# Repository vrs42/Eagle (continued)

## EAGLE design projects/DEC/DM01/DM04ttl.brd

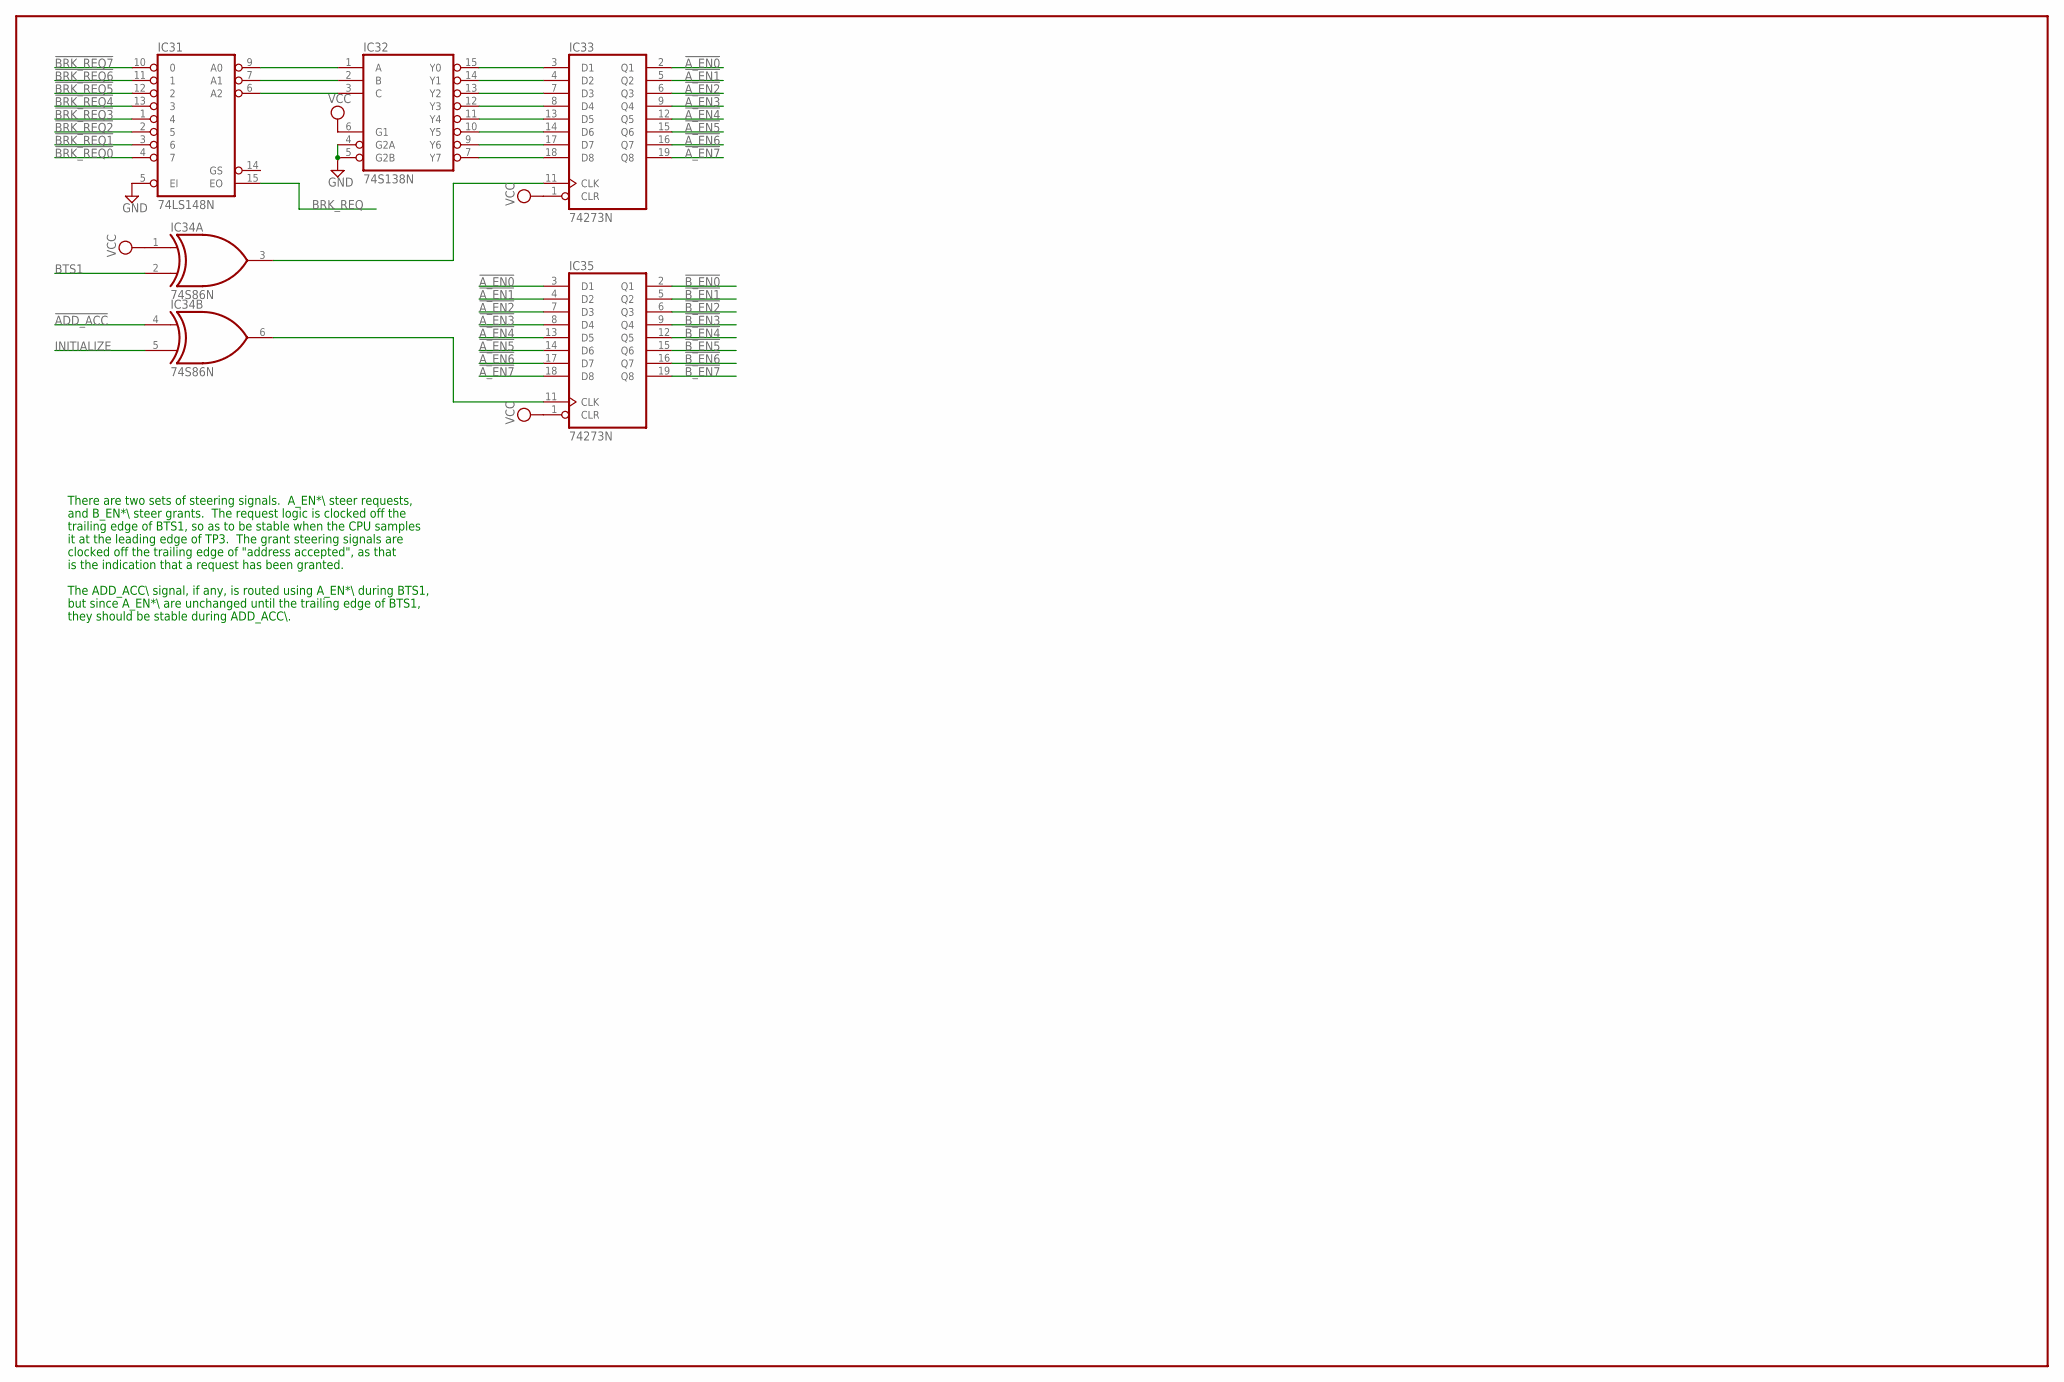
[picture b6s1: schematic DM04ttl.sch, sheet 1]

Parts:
IC31: 74LS148N; DIL16
IC32: 74S138N; DIL16
IC33, IC35: 74273N; DIL20
IC34: 74S86N; DIL14

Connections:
!ADD_ACC: IC34.4 (I0); also elsewhere on the board
!A_EN0: IC33.2 (Q1), IC35.3 (D1); also elsewhere on the board
!A_EN1: IC33.5 (Q2), IC35.4 (D2); also elsewhere on the board
!A_EN2: IC33.6 (Q3), IC35.7 (D3); also elsewhere on the board
!A_EN3: IC33.9 (Q4), IC35.8 (D4); also elsewhere on the board
!A_EN4: IC33.12 (Q5), IC35.13 (D5); also elsewhere on the board
!A_EN5: IC33.15 (Q6), IC35.14 (D6); also elsewhere on the board
!A_EN6: IC33.16 (Q7), IC35.17 (D7); also elsewhere on the board
!A_EN7: IC33.19 (Q8), IC35.18 (D8); also elsewhere on the board
!BRK_REQ0: IC31.4 (7); also elsewhere on the board
!BRK_REQ1: IC31.3 (6); also elsewhere on the board
!BRK_REQ2: IC31.2 (5); also elsewhere on the board
!BRK_REQ3: IC31.1 (4); also elsewhere on the board
!BRK_REQ4: IC31.13 (3); also elsewhere on the board
!BRK_REQ5: IC31.12 (2); also elsewhere on the board
!BRK_REQ6: IC31.11 (1); also elsewhere on the board
!BRK_REQ7: IC31.10 (0); also elsewhere on the board
!B_EN0: IC35.2 (Q1); also elsewhere on the board
!B_EN1: IC35.5 (Q2); also elsewhere on the board
!B_EN2: IC35.6 (Q3); also elsewhere on the board
!B_EN3: IC35.9 (Q4); also elsewhere on the board
!B_EN4: IC35.12 (Q5); also elsewhere on the board
!B_EN5: IC35.15 (Q6); also elsewhere on the board
!B_EN6: IC35.16 (Q7); also elsewhere on the board
!B_EN7: IC35.19 (Q8); also elsewhere on the board
BRK_REQ: IC31.15 (EO); also elsewhere on the board
BTS1: IC34.2 (I1); also elsewhere on the board
GND: IC31.5 (EI), IC31.8 (GND), IC32.4 (G2A), IC32.5 (G2B), IC32.8 (GND), IC33.10 (GND), IC34.7 (GND), IC35.10 (GND); also elsewhere on the board
INITIALIZE: IC34.5 (I1); also elsewhere on the board
unnamed: IC31.6 (A2), IC32.3 (C)
unnamed: IC34.6 (O), IC35.11 (CLK)
unnamed: IC31.7 (A1), IC32.2 (B)
unnamed: IC31.9 (A0), IC32.1 (A)
unnamed: IC32.15 (Y0), IC33.3 (D1)
unnamed: IC32.7 (Y7), IC33.18 (D8)
unnamed: IC32.9 (Y6), IC33.17 (D7)
unnamed: IC32.10 (Y5), IC33.14 (D6)
unnamed: IC32.11 (Y4), IC33.13 (D5)
unnamed: IC32.12 (Y3), IC33.8 (D4)
unnamed: IC32.13 (Y2), IC33.7 (D3)
unnamed: IC32.14 (Y1), IC33.4 (D2)
unnamed: IC33.11 (CLK), IC34.3 (O)
VCC: IC31.16 (VCC), IC32.6 (G1), IC32.16 (VCC), IC33.1 (CLR), IC33.20 (VCC), IC34.1 (I0), IC34.14 (VCC), IC35.1 (CLR), IC35.20 (VCC); also elsewhere on the board

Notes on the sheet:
There are two sets of steering signals. A_EN*\\ steer requests,
and B_EN*\\ steer grants. The request logic is clocked off the
trailing edge of BTS1, so as to be stable when the CPU samples
it at the leading edge of TP3. The grant steering signals are
clocked off the trailing edge of "address accepted", as that
is the indication that a request has been granted.
The ADD_ACC\\ signal, if any, is routed using A_EN*\\ during BTS1,
but since A_EN*\\ are unchanged until the trailing edge of BTS1,
they should be stable during ADD_ACC\\.

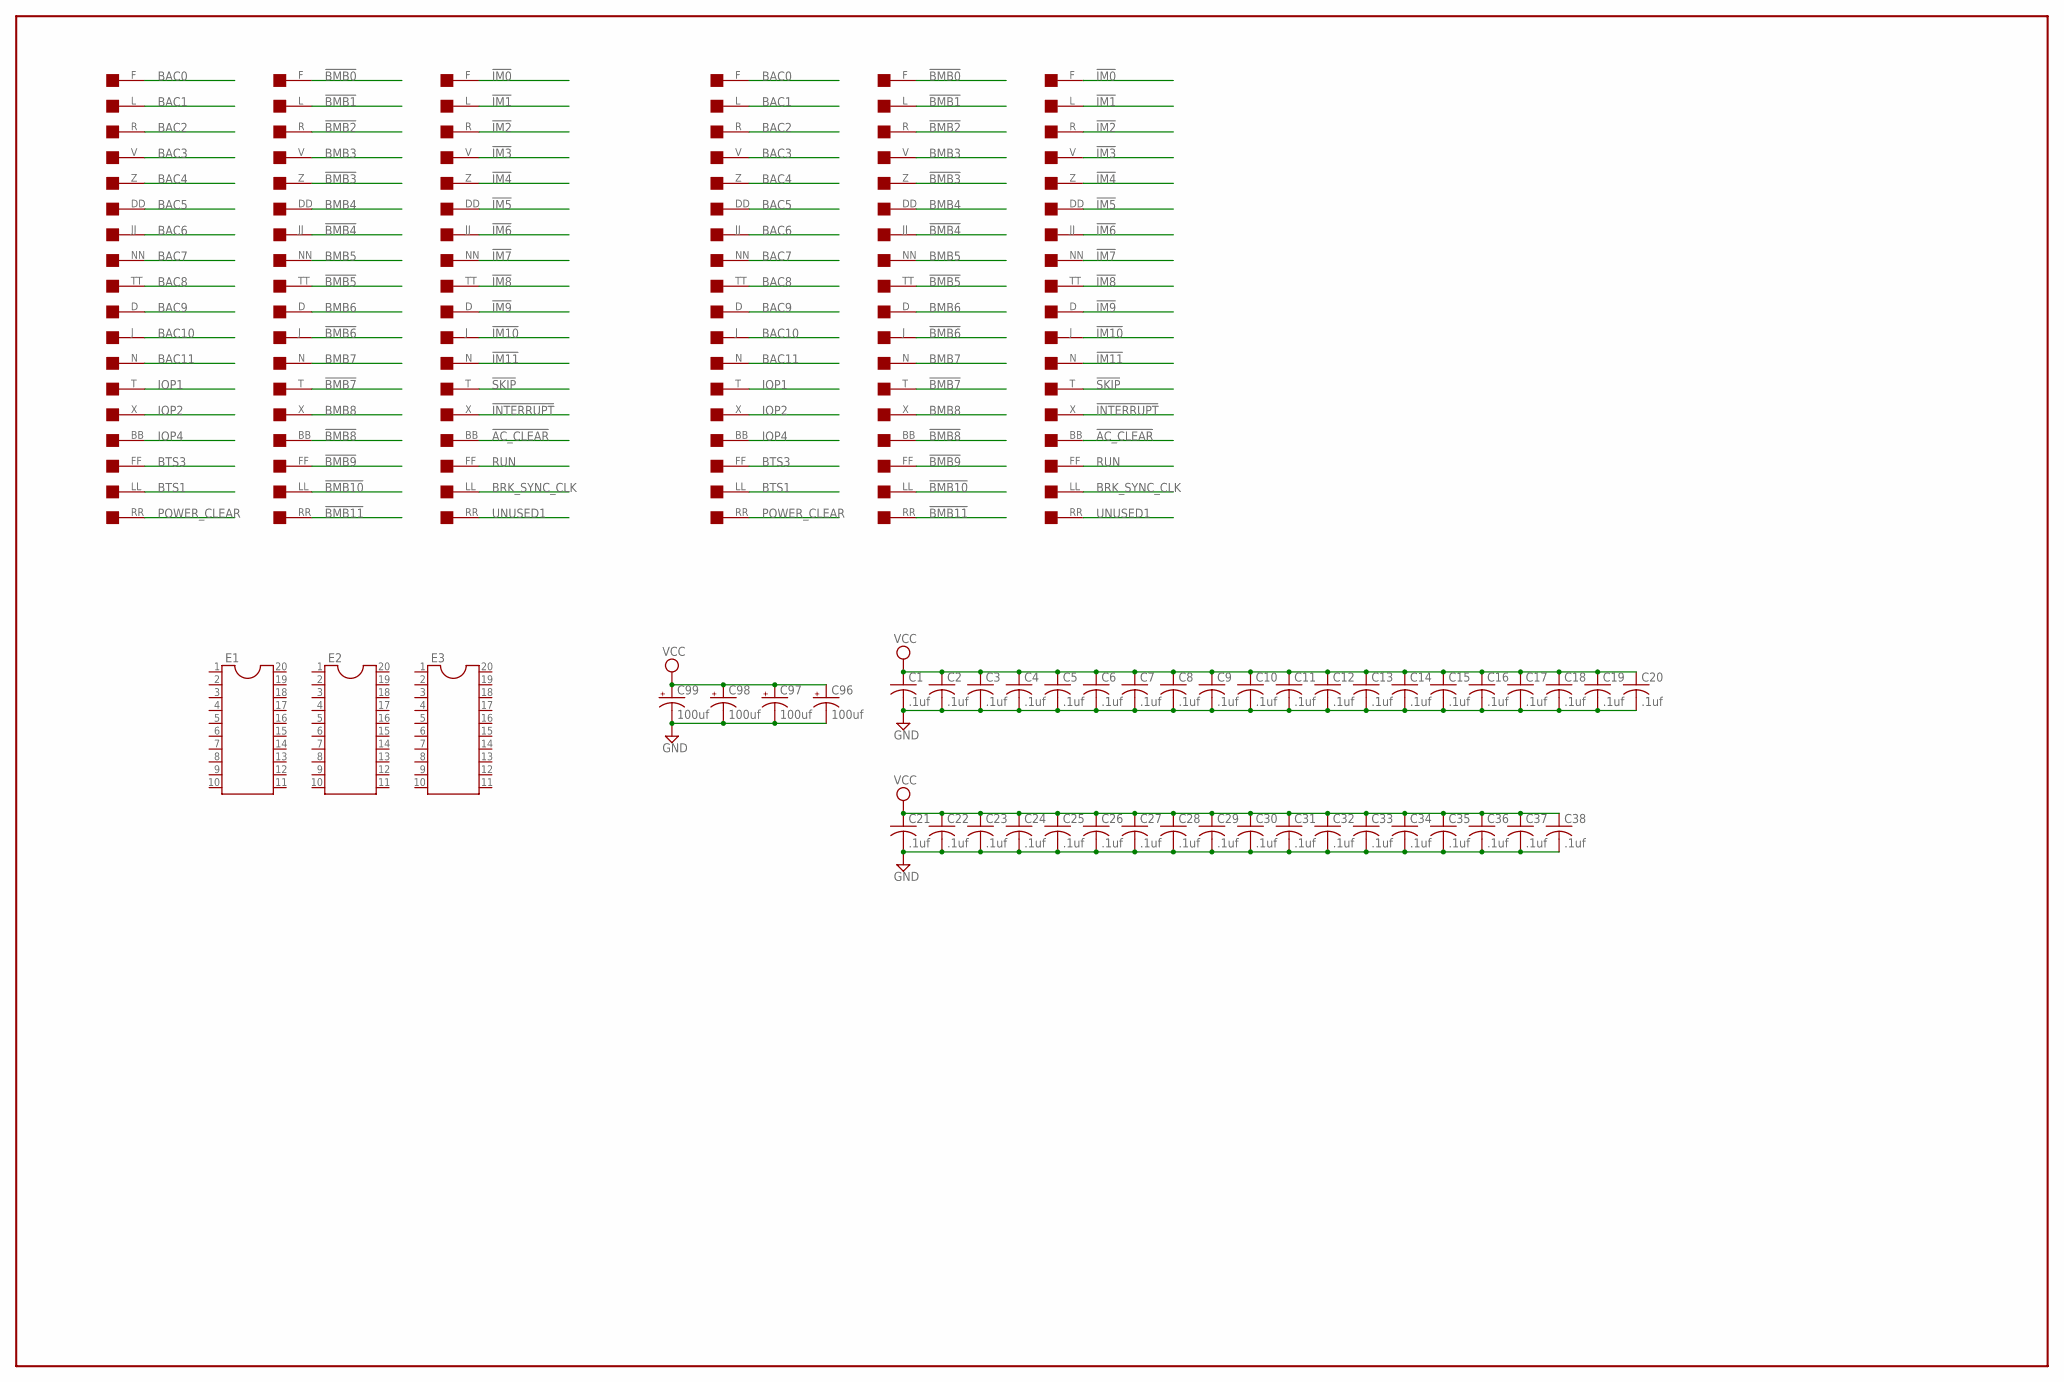
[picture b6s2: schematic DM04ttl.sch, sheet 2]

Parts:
AC0, AC1: BC08J; DEC40PINV
BAC0, BAC1: BC08J; DEC40PINV
BMB0, BMB1: BC08J; DEC40PINV
C1, C2, C3, C4, C5, C6, C7, C8, C9, C10, C11, C12, C13, C14, C15, C16, C17, C18, C19, C20, C21, C22, C23, C24, C25, C26, C27, C28, C29, C30, C31, C32, C33, C34, C35, C36, C37, C38: .1uf; C050-025X075
C96, C97, C98, C99: 100uf; E22-6
E1, E2, E3: DIL20

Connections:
!AC_CLEAR: AC0.BB (1), AC1.BB (1)
!BMB0: BMB0.F (1), BMB1.F (1)
!BMB1: BMB0.L (1), BMB1.L (1)
!BMB2: BMB0.R (1), BMB1.R (1)
!BMB3: BMB0.Z (1), BMB1.Z (1)
!BMB4: BMB0.JJ (1), BMB1.JJ (1)
!BMB5: BMB0.TT (1), BMB1.TT (1)
!BMB6: BMB0.J (1), BMB1.J (1)
!BMB7: BMB0.T (1), BMB1.T (1)
!BMB8: BMB0.BB (1), BMB1.BB (1)
!BMB9: BMB0.FF (1), BMB1.FF (1)
!BMB10: BMB0.LL (1), BMB1.LL (1)
!BMB11: BMB0.RR (1), BMB1.RR (1)
!IM0: AC0.F (1), AC1.F (1)
!IM1: AC0.L (1), AC1.L (1)
!IM2: AC0.R (1), AC1.R (1)
!IM3: AC0.V (1), AC1.V (1)
!IM4: AC0.Z (1), AC1.Z (1)
!IM5: AC0.DD (1), AC1.DD (1)
!IM6: AC0.JJ (1), AC1.JJ (1)
!IM7: AC0.NN (1), AC1.NN (1)
!IM8: AC0.TT (1), AC1.TT (1)
!IM9: AC0.D (1), AC1.D (1)
!IM10: AC0.J (1), AC1.J (1)
!IM11: AC0.N (1), AC1.N (1)
!INTERRUPT: AC0.X (1), AC1.X (1)
!SKIP: AC0.T (1), AC1.T (1)
BAC0: BAC0.F (1), BAC1.F (1)
BAC1: BAC0.L (1), BAC1.L (1)
BAC2: BAC0.R (1), BAC1.R (1)
BAC3: BAC0.V (1), BAC1.V (1)
BAC4: BAC0.Z (1), BAC1.Z (1)
BAC5: BAC0.DD (1), BAC1.DD (1)
BAC6: BAC0.JJ (1), BAC1.JJ (1)
BAC7: BAC0.NN (1), BAC1.NN (1)
BAC8: BAC0.TT (1), BAC1.TT (1)
BAC9: BAC0.D (1), BAC1.D (1)
BAC10: BAC0.J (1), BAC1.J (1)
BAC11: BAC0.N (1), BAC1.N (1)
BMB3: BMB0.V (1), BMB1.V (1)
BMB4: BMB0.DD (1), BMB1.DD (1)
BMB5: BMB0.NN (1), BMB1.NN (1)
BMB6: BMB0.D (1), BMB1.D (1)
BMB7: BMB0.N (1), BMB1.N (1)
BMB8: BMB0.X (1), BMB1.X (1)
BRK_SYNC_CLK: AC0.LL (1), AC1.LL (1)
BTS1: BAC0.LL (1), BAC1.LL (1); also elsewhere on the board
BTS3: BAC0.FF (1), BAC1.FF (1)
GND: AC0.A (GND), AC0.AA (GND), AC0.B (GND), AC0.C (GND), AC0.CC (GND), AC0.E (GND), AC0.EE (GND), AC0.H (GND), AC0.HH (GND), AC0.K (GND), AC0.KK (GND), AC0.M (GND), AC0.MM (GND), AC0.P (GND), AC0.PP (GND), AC0.S (GND), AC0.SS (GND), AC0.U (GND), AC0.UU (GND), AC0.VV (GND), AC0.W (GND), AC0.Y (GND), AC1.A (GND), AC1.AA (GND), AC1.B (GND), AC1.C (GND), AC1.CC (GND), AC1.E (GND), AC1.EE (GND), AC1.H (GND), AC1.HH (GND), AC1.K (GND), AC1.KK (GND), AC1.M (GND), AC1.MM (GND), AC1.P (GND), AC1.PP (GND), AC1.S (GND), AC1.SS (GND), AC1.U (GND), AC1.UU (GND), AC1.VV (GND), AC1.W (GND), AC1.Y (GND), BAC0.A (GND), BAC0.AA (GND), BAC0.B (GND), BAC0.C (GND), BAC0.CC (GND), BAC0.E (GND), BAC0.EE (GND), BAC0.H (GND), BAC0.HH (GND), BAC0.K (GND), BAC0.KK (GND), BAC0.M (GND), BAC0.MM (GND), BAC0.P (GND), BAC0.PP (GND), BAC0.S (GND), BAC0.SS (GND), BAC0.U (GND), BAC0.UU (GND), BAC0.VV (GND), BAC0.W (GND), BAC0.Y (GND), BAC1.A (GND), BAC1.AA (GND), BAC1.B (GND), BAC1.C (GND), BAC1.CC (GND), BAC1.E (GND), BAC1.EE (GND), BAC1.H (GND), BAC1.HH (GND), BAC1.K (GND), BAC1.KK (GND), BAC1.M (GND), BAC1.MM (GND), BAC1.P (GND), BAC1.PP (GND), BAC1.S (GND), BAC1.SS (GND), BAC1.U (GND), BAC1.UU (GND), BAC1.VV (GND), BAC1.W (GND), BAC1.Y (GND), BMB0.A (GND), BMB0.AA (GND), BMB0.B (GND), BMB0.C (GND), BMB0.CC (GND), BMB0.E (GND), BMB0.EE (GND), BMB0.H (GND), BMB0.HH (GND), BMB0.K (GND), BMB0.KK (GND), BMB0.M (GND), BMB0.MM (GND), BMB0.P (GND), BMB0.PP (GND), BMB0.S (GND), BMB0.SS (GND), BMB0.U (GND), BMB0.UU (GND), BMB0.VV (GND), BMB0.W (GND), BMB0.Y (GND), BMB1.A (GND), BMB1.AA (GND), BMB1.B (GND), BMB1.C (GND), BMB1.CC (GND), BMB1.E (GND), BMB1.EE (GND), BMB1.H (GND), BMB1.HH (GND), BMB1.K (GND), BMB1.KK (GND), BMB1.M (GND), BMB1.MM (GND), BMB1.P (GND), BMB1.PP (GND), BMB1.S (GND), BMB1.SS (GND), BMB1.U (GND), BMB1.UU (GND), BMB1.VV (GND), BMB1.W (GND), BMB1.Y (GND), C1.2, C2.2, C3.2, C4.2, C5.2, C6.2, C7.2, C8.2, C9.2, C10.2, C11.2, C12.2, C13.2, C14.2, C15.2, C16.2, C17.2, C18.2, C19.2, C20.2, C21.2, C22.2, C23.2, C24.2, C25.2, C26.2, C27.2, C28.2, C29.2, C30.2, C31.2, C32.2, C33.2, C34.2, C35.2, C36.2, C37.2, C38.2, C96.-, C97.-, C98.-, C99.-; also elsewhere on the board
IOP1: BAC0.T (1), BAC1.T (1)
IOP2: BAC0.X (1), BAC1.X (1)
IOP4: BAC0.BB (1), BAC1.BB (1)
POWER_CLEAR: BAC0.RR (1), BAC1.RR (1)
RUN: AC0.FF (1), AC1.FF (1)
UNUSED1: AC0.RR (1), AC1.RR (1)
VCC: C1.1, C2.1, C3.1, C4.1, C5.1, C6.1, C7.1, C8.1, C9.1, C10.1, C11.1, C12.1, C13.1, C14.1, C15.1, C16.1, C17.1, C18.1, C19.1, C20.1, C21.1, C22.1, C23.1, C24.1, C25.1, C26.1, C27.1, C28.1, C29.1, C30.1, C31.1, C32.1, C33.1, C34.1, C35.1, C36.1, C37.1, C38.1, C96.+, C97.+, C98.+, C99.+; also elsewhere on the board

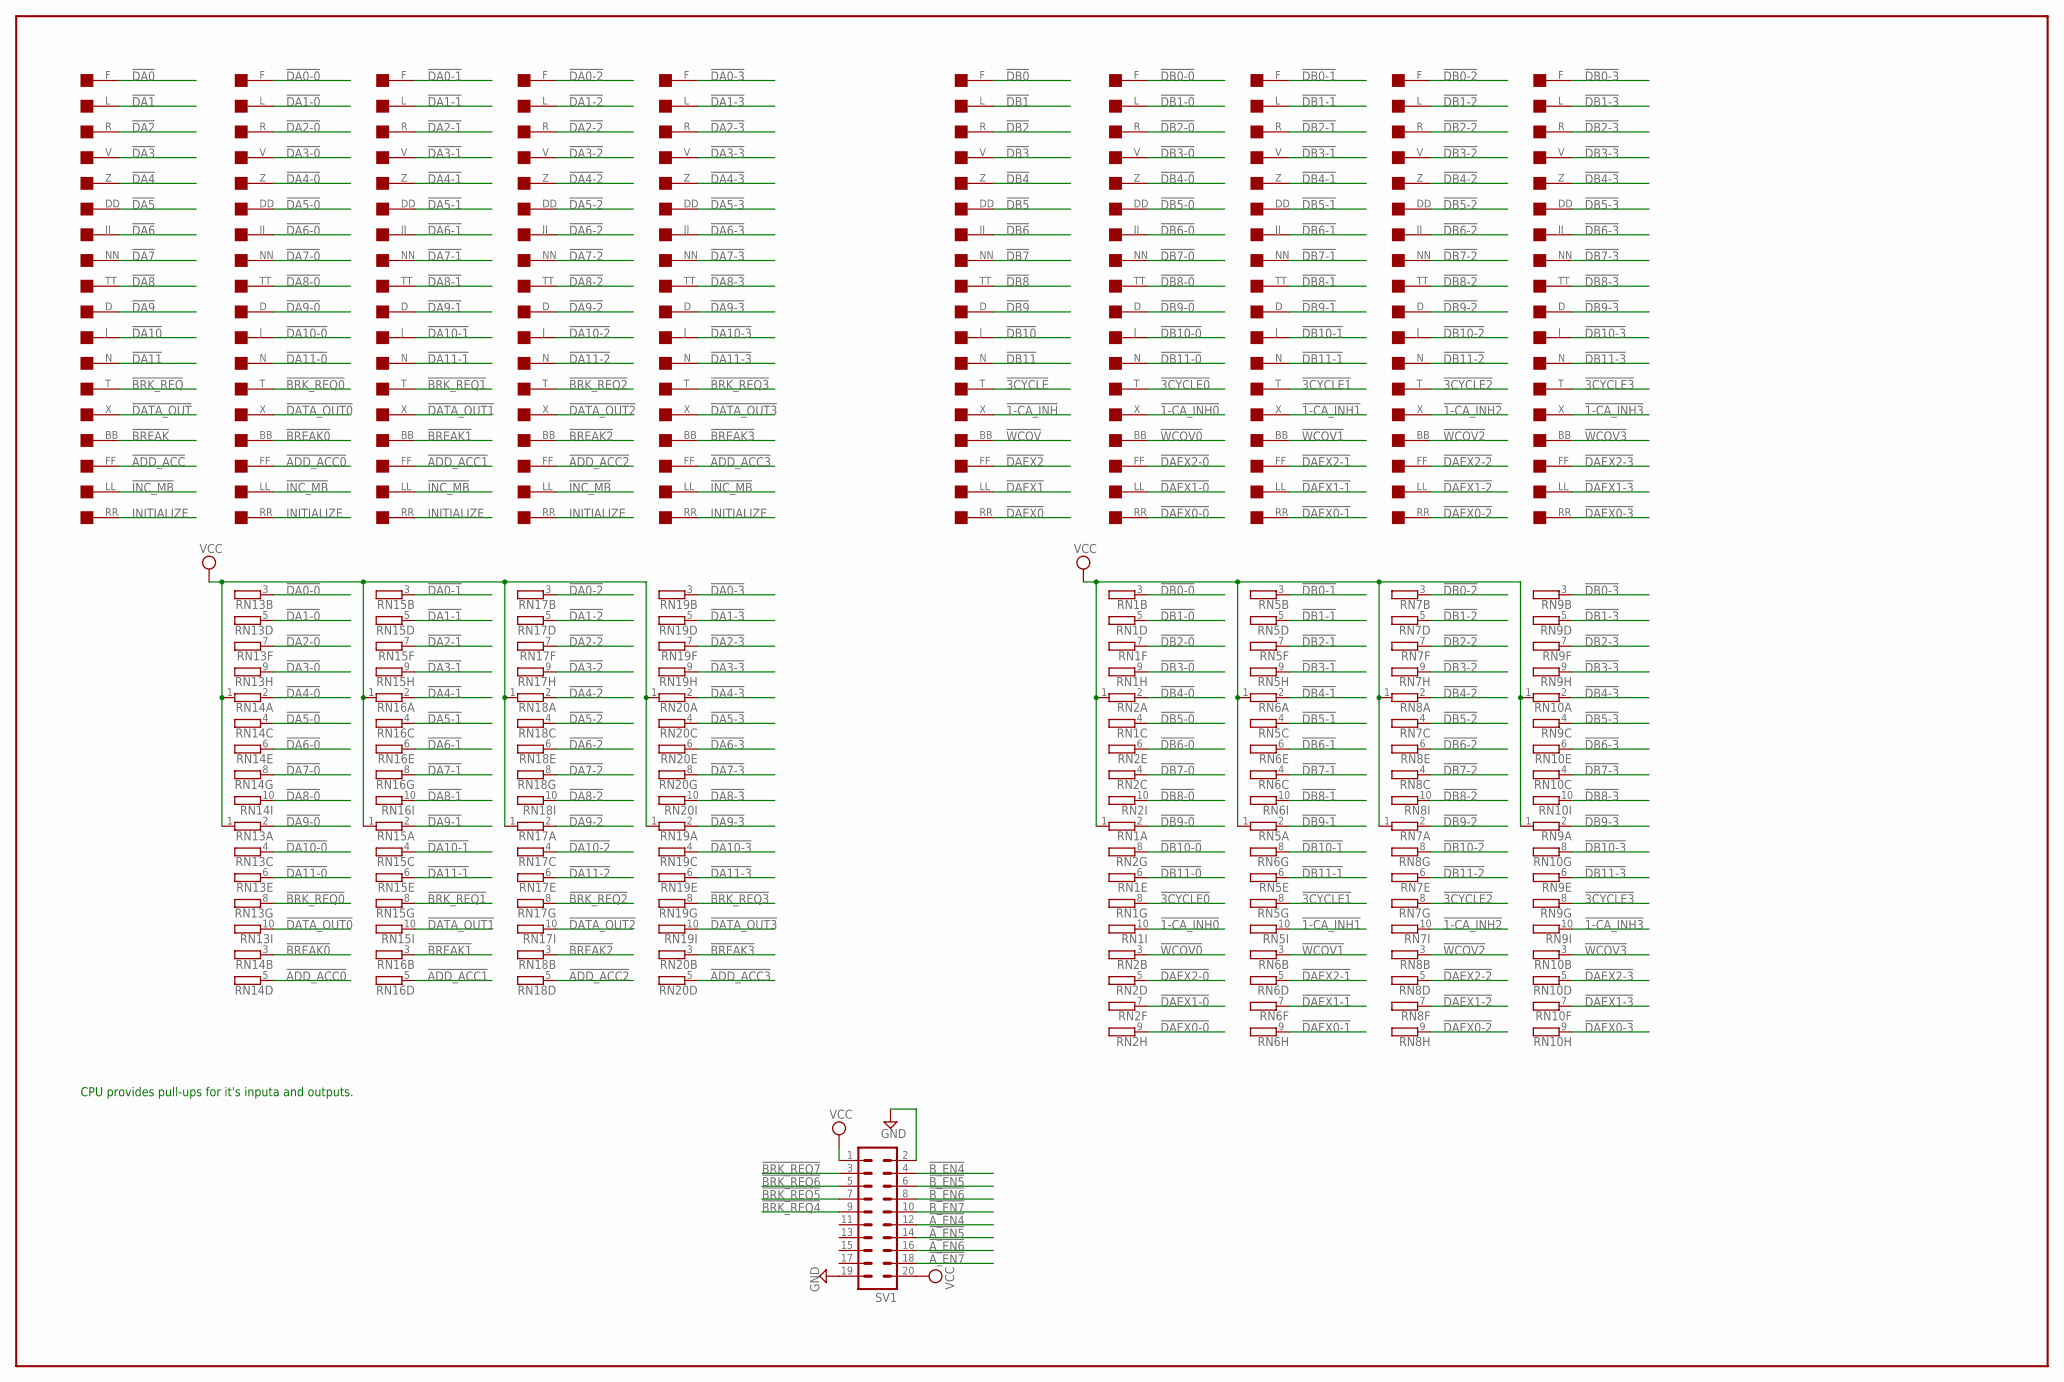
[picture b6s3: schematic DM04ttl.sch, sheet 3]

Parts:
ADDRESS, ADDRESS0, ADDRESS1, ADDRESS2, ADDRESS3: BC08J; DEC40PINV
DATA, DATA0, DATA1, DATA2, DATA3: BC08J; DEC40PINV
RN1, RN2, RN5, RN6, RN7, RN8, RN9, RN10, RN13, RN14, RN15, RN16, RN17, RN18, RN19, RN20: GE09R; SIL10
SV1: MA10-2

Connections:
!1-CA_INH: DATA.X (1); also elsewhere on the board
!1-CA_INH0: DATA0.X (1), RN1.10 (2); also elsewhere on the board
!1-CA_INH1: DATA1.X (1), RN5.10 (2); also elsewhere on the board
!1-CA_INH2: DATA2.X (1), RN7.10 (2); also elsewhere on the board
!1-CA_INH3: DATA3.X (1), RN9.10 (2); also elsewhere on the board
!3CYCLE: DATA.T (1); also elsewhere on the board
!3CYCLE0: DATA0.T (1), RN1.8 (2); also elsewhere on the board
!3CYCLE1: DATA1.T (1), RN5.8 (2); also elsewhere on the board
!3CYCLE2: DATA2.T (1), RN7.8 (2); also elsewhere on the board
!3CYCLE3: DATA3.T (1), RN9.8 (2); also elsewhere on the board
!ADD_ACC: ADDRESS.FF (1); also elsewhere on the board
!ADD_ACC0: ADDRESS0.FF (1), RN14.5 (2); also elsewhere on the board
!ADD_ACC1: ADDRESS1.FF (1), RN16.5 (2); also elsewhere on the board
!ADD_ACC2: ADDRESS2.FF (1), RN18.5 (2); also elsewhere on the board
!ADD_ACC3: ADDRESS3.FF (1), RN20.5 (2); also elsewhere on the board
!A_EN4: SV1.12; also elsewhere on the board
!A_EN5: SV1.14; also elsewhere on the board
!A_EN6: SV1.16; also elsewhere on the board
!A_EN7: SV1.18; also elsewhere on the board
!BREAK: ADDRESS.BB (1); also elsewhere on the board
!BREAK0: ADDRESS0.BB (1), RN14.3 (2); also elsewhere on the board
!BREAK1: ADDRESS1.BB (1), RN16.3 (2); also elsewhere on the board
!BREAK2: ADDRESS2.BB (1), RN18.3 (2); also elsewhere on the board
!BREAK3: ADDRESS3.BB (1), RN20.3 (2); also elsewhere on the board
!BRK_REQ: ADDRESS.T (1); also elsewhere on the board
!BRK_REQ0: ADDRESS0.T (1), RN13.8 (2); also elsewhere on the board
!BRK_REQ1: ADDRESS1.T (1), RN15.8 (2); also elsewhere on the board
!BRK_REQ2: ADDRESS2.T (1), RN17.8 (2); also elsewhere on the board
!BRK_REQ3: ADDRESS3.T (1), RN19.8 (2); also elsewhere on the board
!BRK_REQ4: SV1.9; also elsewhere on the board
!BRK_REQ5: SV1.7; also elsewhere on the board
!BRK_REQ6: SV1.5; also elsewhere on the board
!BRK_REQ7: SV1.3; also elsewhere on the board
!B_EN4: SV1.4; also elsewhere on the board
!B_EN5: SV1.6; also elsewhere on the board
!B_EN6: SV1.8; also elsewhere on the board
!B_EN7: SV1.10; also elsewhere on the board
!DA0: ADDRESS.F (1); also elsewhere on the board
!DA0-0: ADDRESS0.F (1), RN13.3 (2); also elsewhere on the board
!DA0-1: ADDRESS1.F (1), RN15.3 (2); also elsewhere on the board
!DA0-2: ADDRESS2.F (1), RN17.3 (2); also elsewhere on the board
!DA0-3: ADDRESS3.F (1), RN19.3 (2); also elsewhere on the board
!DA1: ADDRESS.L (1); also elsewhere on the board
!DA1-0: ADDRESS0.L (1), RN13.5 (2); also elsewhere on the board
!DA1-1: ADDRESS1.L (1), RN15.5 (2); also elsewhere on the board
!DA1-2: ADDRESS2.L (1), RN17.5 (2); also elsewhere on the board
!DA1-3: ADDRESS3.L (1), RN19.5 (2); also elsewhere on the board
!DA2: ADDRESS.R (1); also elsewhere on the board
!DA2-0: ADDRESS0.R (1), RN13.7 (2); also elsewhere on the board
!DA2-1: ADDRESS1.R (1), RN15.7 (2); also elsewhere on the board
!DA2-2: ADDRESS2.R (1), RN17.7 (2); also elsewhere on the board
!DA2-3: ADDRESS3.R (1), RN19.7 (2); also elsewhere on the board
!DA3: ADDRESS.V (1); also elsewhere on the board
!DA3-0: ADDRESS0.V (1), RN13.9 (2); also elsewhere on the board
!DA3-1: ADDRESS1.V (1), RN15.9 (2); also elsewhere on the board
!DA3-2: ADDRESS2.V (1), RN17.9 (2); also elsewhere on the board
!DA3-3: ADDRESS3.V (1), RN19.9 (2); also elsewhere on the board
!DA4: ADDRESS.Z (1); also elsewhere on the board
!DA4-0: ADDRESS0.Z (1), RN14.2; also elsewhere on the board
!DA4-1: ADDRESS1.Z (1), RN16.2; also elsewhere on the board
!DA4-2: ADDRESS2.Z (1), RN18.2; also elsewhere on the board
!DA4-3: ADDRESS3.Z (1), RN20.2; also elsewhere on the board
!DA5: ADDRESS.DD (1); also elsewhere on the board
!DA5-0: ADDRESS0.DD (1), RN14.4 (2); also elsewhere on the board
!DA5-1: ADDRESS1.DD (1), RN16.4 (2); also elsewhere on the board
!DA5-2: ADDRESS2.DD (1), RN18.4 (2); also elsewhere on the board
!DA5-3: ADDRESS3.DD (1), RN20.4 (2); also elsewhere on the board
!DA6: ADDRESS.JJ (1); also elsewhere on the board
!DA6-0: ADDRESS0.JJ (1), RN14.6 (2); also elsewhere on the board
!DA6-1: ADDRESS1.JJ (1), RN16.6 (2); also elsewhere on the board
!DA6-2: ADDRESS2.JJ (1), RN18.6 (2); also elsewhere on the board
!DA6-3: ADDRESS3.JJ (1), RN20.6 (2); also elsewhere on the board
!DA7: ADDRESS.NN (1); also elsewhere on the board
!DA7-0: ADDRESS0.NN (1), RN14.8 (2); also elsewhere on the board
!DA7-1: ADDRESS1.NN (1), RN16.8 (2); also elsewhere on the board
!DA7-2: ADDRESS2.NN (1), RN18.8 (2); also elsewhere on the board
!DA7-3: ADDRESS3.NN (1), RN20.8 (2); also elsewhere on the board
!DA8: ADDRESS.TT (1); also elsewhere on the board
!DA8-0: ADDRESS0.TT (1), RN14.10 (2); also elsewhere on the board
!DA8-1: ADDRESS1.TT (1), RN16.10 (2); also elsewhere on the board
!DA8-2: ADDRESS2.TT (1), RN18.10 (2); also elsewhere on the board
!DA8-3: ADDRESS3.TT (1), RN20.10 (2); also elsewhere on the board
!DA9: ADDRESS.D (1); also elsewhere on the board
!DA9-0: ADDRESS0.D (1), RN13.2; also elsewhere on the board
!DA9-1: ADDRESS1.D (1), RN15.2; also elsewhere on the board
!DA9-2: ADDRESS2.D (1), RN17.2; also elsewhere on the board
!DA9-3: ADDRESS3.D (1), RN19.2; also elsewhere on the board
!DA10: ADDRESS.J (1); also elsewhere on the board
!DA10-0: ADDRESS0.J (1), RN13.4 (2); also elsewhere on the board
!DA10-1: ADDRESS1.J (1), RN15.4 (2); also elsewhere on the board
!DA10-2: ADDRESS2.J (1), RN17.4 (2); also elsewhere on the board
!DA10-3: ADDRESS3.J (1), RN19.4 (2); also elsewhere on the board
!DA11: ADDRESS.N (1); also elsewhere on the board
!DA11-0: ADDRESS0.N (1), RN13.6 (2); also elsewhere on the board
!DA11-1: ADDRESS1.N (1), RN15.6 (2); also elsewhere on the board
!DA11-2: ADDRESS2.N (1), RN17.6 (2); also elsewhere on the board
!DA11-3: ADDRESS3.N (1), RN19.6 (2); also elsewhere on the board
!DAEX0: DATA.RR (1); also elsewhere on the board
!DAEX0-0: DATA0.RR (1), RN2.9 (2); also elsewhere on the board
!DAEX0-1: DATA1.RR (1), RN6.9 (2); also elsewhere on the board
!DAEX0-2: DATA2.RR (1), RN8.9 (2); also elsewhere on the board
!DAEX0-3: DATA3.RR (1), RN10.9 (2); also elsewhere on the board
!DAEX1: DATA.LL (1); also elsewhere on the board
!DAEX1-0: DATA0.LL (1), RN2.7 (2); also elsewhere on the board
!DAEX1-1: DATA1.LL (1), RN6.7 (2); also elsewhere on the board
!DAEX1-2: DATA2.LL (1), RN8.7 (2); also elsewhere on the board
!DAEX1-3: DATA3.LL (1), RN10.7 (2); also elsewhere on the board
!DAEX2: DATA.FF (1); also elsewhere on the board
!DAEX2-0: DATA0.FF (1), RN2.5 (2); also elsewhere on the board
!DAEX2-1: DATA1.FF (1), RN6.5 (2); also elsewhere on the board
!DAEX2-2: DATA2.FF (1), RN8.5 (2); also elsewhere on the board
!DAEX2-3: DATA3.FF (1), RN10.5 (2); also elsewhere on the board
!DATA_OUT: ADDRESS.X (1); also elsewhere on the board
!DATA_OUT0: ADDRESS0.X (1), RN13.10 (2); also elsewhere on the board
!DATA_OUT1: ADDRESS1.X (1), RN15.10 (2); also elsewhere on the board
!DATA_OUT2: ADDRESS2.X (1), RN17.10 (2); also elsewhere on the board
!DATA_OUT3: ADDRESS3.X (1), RN19.10 (2); also elsewhere on the board
!DB0: DATA.F (1); also elsewhere on the board
!DB0-0: DATA0.F (1), RN1.3 (2); also elsewhere on the board
!DB0-1: DATA1.F (1), RN5.3 (2); also elsewhere on the board
!DB0-2: DATA2.F (1), RN7.3 (2); also elsewhere on the board
!DB0-3: DATA3.F (1), RN9.3 (2); also elsewhere on the board
!DB1: DATA.L (1); also elsewhere on the board
!DB1-0: DATA0.L (1), RN1.5 (2); also elsewhere on the board
!DB1-1: DATA1.L (1), RN5.5 (2); also elsewhere on the board
!DB1-2: DATA2.L (1), RN7.5 (2); also elsewhere on the board
!DB1-3: DATA3.L (1), RN9.5 (2); also elsewhere on the board
!DB2: DATA.R (1); also elsewhere on the board
!DB2-0: DATA0.R (1), RN1.7 (2); also elsewhere on the board
!DB2-1: DATA1.R (1), RN5.7 (2); also elsewhere on the board
!DB2-2: DATA2.R (1), RN7.7 (2); also elsewhere on the board
!DB2-3: DATA3.R (1), RN9.7 (2); also elsewhere on the board
!DB3: DATA.V (1); also elsewhere on the board
!DB3-0: DATA0.V (1), RN1.9 (2); also elsewhere on the board
!DB3-1: DATA1.V (1), RN5.9 (2); also elsewhere on the board
!DB3-2: DATA2.V (1), RN7.9 (2); also elsewhere on the board
!DB3-3: DATA3.V (1), RN9.9 (2); also elsewhere on the board
!DB4: DATA.Z (1); also elsewhere on the board
!DB4-0: DATA0.Z (1), RN2.2; also elsewhere on the board
!DB4-1: DATA1.Z (1), RN6.2; also elsewhere on the board
!DB4-2: DATA2.Z (1), RN8.2; also elsewhere on the board
!DB4-3: DATA3.Z (1), RN10.2; also elsewhere on the board
!DB5: DATA.DD (1); also elsewhere on the board
!DB5-0: DATA0.DD (1), RN1.4 (2); also elsewhere on the board
!DB5-1: DATA1.DD (1), RN5.4 (2); also elsewhere on the board
!DB5-2: DATA2.DD (1), RN7.4 (2); also elsewhere on the board
!DB5-3: DATA3.DD (1), RN9.4 (2); also elsewhere on the board
!DB6: DATA.JJ (1); also elsewhere on the board
!DB6-0: DATA0.JJ (1), RN2.6 (2); also elsewhere on the board
!DB6-1: DATA1.JJ (1), RN6.6 (2); also elsewhere on the board
!DB6-2: DATA2.JJ (1), RN8.6 (2); also elsewhere on the board
!DB6-3: DATA3.JJ (1), RN10.6 (2); also elsewhere on the board
!DB7: DATA.NN (1); also elsewhere on the board
!DB7-0: DATA0.NN (1), RN2.4 (2); also elsewhere on the board
!DB7-1: DATA1.NN (1), RN6.4 (2); also elsewhere on the board
!DB7-2: DATA2.NN (1), RN8.4 (2); also elsewhere on the board
!DB7-3: DATA3.NN (1), RN10.4 (2); also elsewhere on the board
!DB8: DATA.TT (1); also elsewhere on the board
!DB8-0: DATA0.TT (1), RN2.10 (2); also elsewhere on the board
!DB8-1: DATA1.TT (1), RN6.10 (2); also elsewhere on the board
!DB8-2: DATA2.TT (1), RN8.10 (2); also elsewhere on the board
!DB8-3: DATA3.TT (1), RN10.10 (2); also elsewhere on the board
!DB9: DATA.D (1); also elsewhere on the board
!DB9-0: DATA0.D (1), RN1.2; also elsewhere on the board
!DB9-1: DATA1.D (1), RN5.2; also elsewhere on the board
!DB9-2: DATA2.D (1), RN7.2; also elsewhere on the board
!DB9-3: DATA3.D (1), RN9.2; also elsewhere on the board
!DB10: DATA.J (1); also elsewhere on the board
!DB10-0: DATA0.J (1), RN2.8 (2); also elsewhere on the board
!DB10-1: DATA1.J (1), RN6.8 (2); also elsewhere on the board
!DB10-2: DATA2.J (1), RN8.8 (2); also elsewhere on the board
!DB10-3: DATA3.J (1), RN10.8 (2); also elsewhere on the board
!DB11: DATA.N (1); also elsewhere on the board
!DB11-0: DATA0.N (1), RN1.6 (2); also elsewhere on the board
!DB11-1: DATA1.N (1), RN5.6 (2); also elsewhere on the board
!DB11-2: DATA2.N (1), RN7.6 (2); also elsewhere on the board
!DB11-3: DATA3.N (1), RN9.6 (2); also elsewhere on the board
!INC_MB: ADDRESS.LL (1), ADDRESS0.LL (1), ADDRESS1.LL (1), ADDRESS2.LL (1), ADDRESS3.LL (1)
!WCOV: DATA.BB (1); also elsewhere on the board
!WCOV0: DATA0.BB (1), RN2.3 (2); also elsewhere on the board
!WCOV1: DATA1.BB (1), RN6.3 (2); also elsewhere on the board
!WCOV2: DATA2.BB (1), RN8.3 (2); also elsewhere on the board
!WCOV3: DATA3.BB (1), RN10.3 (2); also elsewhere on the board
GND: ADDRESS.A (GND), ADDRESS.AA (GND), ADDRESS.B (GND), ADDRESS.C (GND), ADDRESS.CC (GND), ADDRESS.E (GND), ADDRESS.EE (GND), ADDRESS.H (GND), ADDRESS.HH (GND), ADDRESS.K (GND), ADDRESS.KK (GND), ADDRESS.M (GND), ADDRESS.MM (GND), ADDRESS.P (GND), ADDRESS.PP (GND), ADDRESS.S (GND), ADDRESS.SS (GND), ADDRESS.U (GND), ADDRESS.UU (GND), ADDRESS.VV (GND), ADDRESS.W (GND), ADDRESS.Y (GND), ADDRESS0.A (GND), ADDRESS0.AA (GND), ADDRESS0.B (GND), ADDRESS0.C (GND), ADDRESS0.CC (GND), ADDRESS0.E (GND), ADDRESS0.EE (GND), ADDRESS0.H (GND), ADDRESS0.HH (GND), ADDRESS0.K (GND), ADDRESS0.KK (GND), ADDRESS0.M (GND), ADDRESS0.MM (GND), ADDRESS0.P (GND), ADDRESS0.PP (GND), ADDRESS0.S (GND), ADDRESS0.SS (GND), ADDRESS0.U (GND), ADDRESS0.UU (GND), ADDRESS0.VV (GND), ADDRESS0.W (GND), ADDRESS0.Y (GND), ADDRESS1.A (GND), ADDRESS1.AA (GND), ADDRESS1.B (GND), ADDRESS1.C (GND), ADDRESS1.CC (GND), ADDRESS1.E (GND), ADDRESS1.EE (GND), ADDRESS1.H (GND), ADDRESS1.HH (GND), ADDRESS1.K (GND), ADDRESS1.KK (GND), ADDRESS1.M (GND), ADDRESS1.MM (GND), ADDRESS1.P (GND), ADDRESS1.PP (GND), ADDRESS1.S (GND), ADDRESS1.SS (GND), ADDRESS1.U (GND), ADDRESS1.UU (GND), ADDRESS1.VV (GND), ADDRESS1.W (GND), ADDRESS1.Y (GND), ADDRESS2.A (GND), ADDRESS2.AA (GND), ADDRESS2.B (GND), ADDRESS2.C (GND), ADDRESS2.CC (GND), ADDRESS2.E (GND), ADDRESS2.EE (GND), ADDRESS2.H (GND), ADDRESS2.HH (GND), ADDRESS2.K (GND), ADDRESS2.KK (GND), ADDRESS2.M (GND), ADDRESS2.MM (GND), ADDRESS2.P (GND), ADDRESS2.PP (GND), ADDRESS2.S (GND), ADDRESS2.SS (GND), ADDRESS2.U (GND), ADDRESS2.UU (GND), ADDRESS2.VV (GND), ADDRESS2.W (GND), ADDRESS2.Y (GND), ADDRESS3.A (GND), ADDRESS3.AA (GND), ADDRESS3.B (GND), ADDRESS3.C (GND), ADDRESS3.CC (GND), ADDRESS3.E (GND), ADDRESS3.EE (GND), ADDRESS3.H (GND), ADDRESS3.HH (GND), ADDRESS3.K (GND), ADDRESS3.KK (GND), ADDRESS3.M (GND), ADDRESS3.MM (GND), ADDRESS3.P (GND), ADDRESS3.PP (GND), ADDRESS3.S (GND), ADDRESS3.SS (GND), ADDRESS3.U (GND), ADDRESS3.UU (GND), ADDRESS3.VV (GND), ADDRESS3.W (GND), ADDRESS3.Y (GND), DATA.A (GND), DATA.AA (GND), DATA.B (GND), DATA.C (GND), DATA.CC (GND), DATA.E (GND), DATA.EE (GND), DATA.H (GND), DATA.HH (GND), DATA.K (GND), DATA.KK (GND), DATA.M (GND), DATA.MM (GND), DATA.P (GND), DATA.PP (GND), DATA.S (GND), DATA.SS (GND), DATA.U (GND), DATA.UU (GND), DATA.VV (GND), DATA.W (GND), DATA.Y (GND), DATA0.A (GND), DATA0.AA (GND), DATA0.B (GND), DATA0.C (GND), DATA0.CC (GND), DATA0.E (GND), DATA0.EE (GND), DATA0.H (GND), DATA0.HH (GND), DATA0.K (GND), DATA0.KK (GND), DATA0.M (GND), DATA0.MM (GND), DATA0.P (GND), DATA0.PP (GND), DATA0.S (GND), DATA0.SS (GND), DATA0.U (GND), DATA0.UU (GND), DATA0.VV (GND), DATA0.W (GND), DATA0.Y (GND), DATA1.A (GND), DATA1.AA (GND), DATA1.B (GND), DATA1.C (GND), DATA1.CC (GND), DATA1.E (GND), DATA1.EE (GND), DATA1.H (GND), DATA1.HH (GND), DATA1.K (GND), DATA1.KK (GND), DATA1.M (GND), DATA1.MM (GND), DATA1.P (GND), DATA1.PP (GND), DATA1.S (GND), DATA1.SS (GND), DATA1.U (GND), DATA1.UU (GND), DATA1.VV (GND), DATA1.W (GND), DATA1.Y (GND), DATA2.A (GND), DATA2.AA (GND), DATA2.B (GND), DATA2.C (GND), DATA2.CC (GND), DATA2.E (GND), DATA2.EE (GND), DATA2.H (GND), DATA2.HH (GND), DATA2.K (GND), DATA2.KK (GND), DATA2.M (GND), DATA2.MM (GND), DATA2.P (GND), DATA2.PP (GND), DATA2.S (GND), DATA2.SS (GND), DATA2.U (GND), DATA2.UU (GND), DATA2.VV (GND), DATA2.W (GND), DATA2.Y (GND), DATA3.A (GND), DATA3.AA (GND), DATA3.B (GND), DATA3.C (GND), DATA3.CC (GND), DATA3.E (GND), DATA3.EE (GND), DATA3.H (GND), DATA3.HH (GND), DATA3.K (GND), DATA3.KK (GND), DATA3.M (GND), DATA3.MM (GND), DATA3.P (GND), DATA3.PP (GND), DATA3.S (GND), DATA3.SS (GND), DATA3.U (GND), DATA3.UU (GND), DATA3.VV (GND), DATA3.W (GND), DATA3.Y (GND), SV1.2, SV1.19; also elsewhere on the board
INITIALIZE: ADDRESS.RR (1), ADDRESS0.RR (1), ADDRESS1.RR (1), ADDRESS2.RR (1), ADDRESS3.RR (1); also elsewhere on the board
VCC: RN1.1, RN2.1, RN5.1, RN6.1, RN7.1, RN8.1, RN9.1, RN10.1, RN13.1, RN14.1, RN15.1, RN16.1, RN17.1, RN18.1, RN19.1, RN20.1, SV1.1, SV1.20; also elsewhere on the board

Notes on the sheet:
CPU provides pull-ups for it's inputa and outputs.
